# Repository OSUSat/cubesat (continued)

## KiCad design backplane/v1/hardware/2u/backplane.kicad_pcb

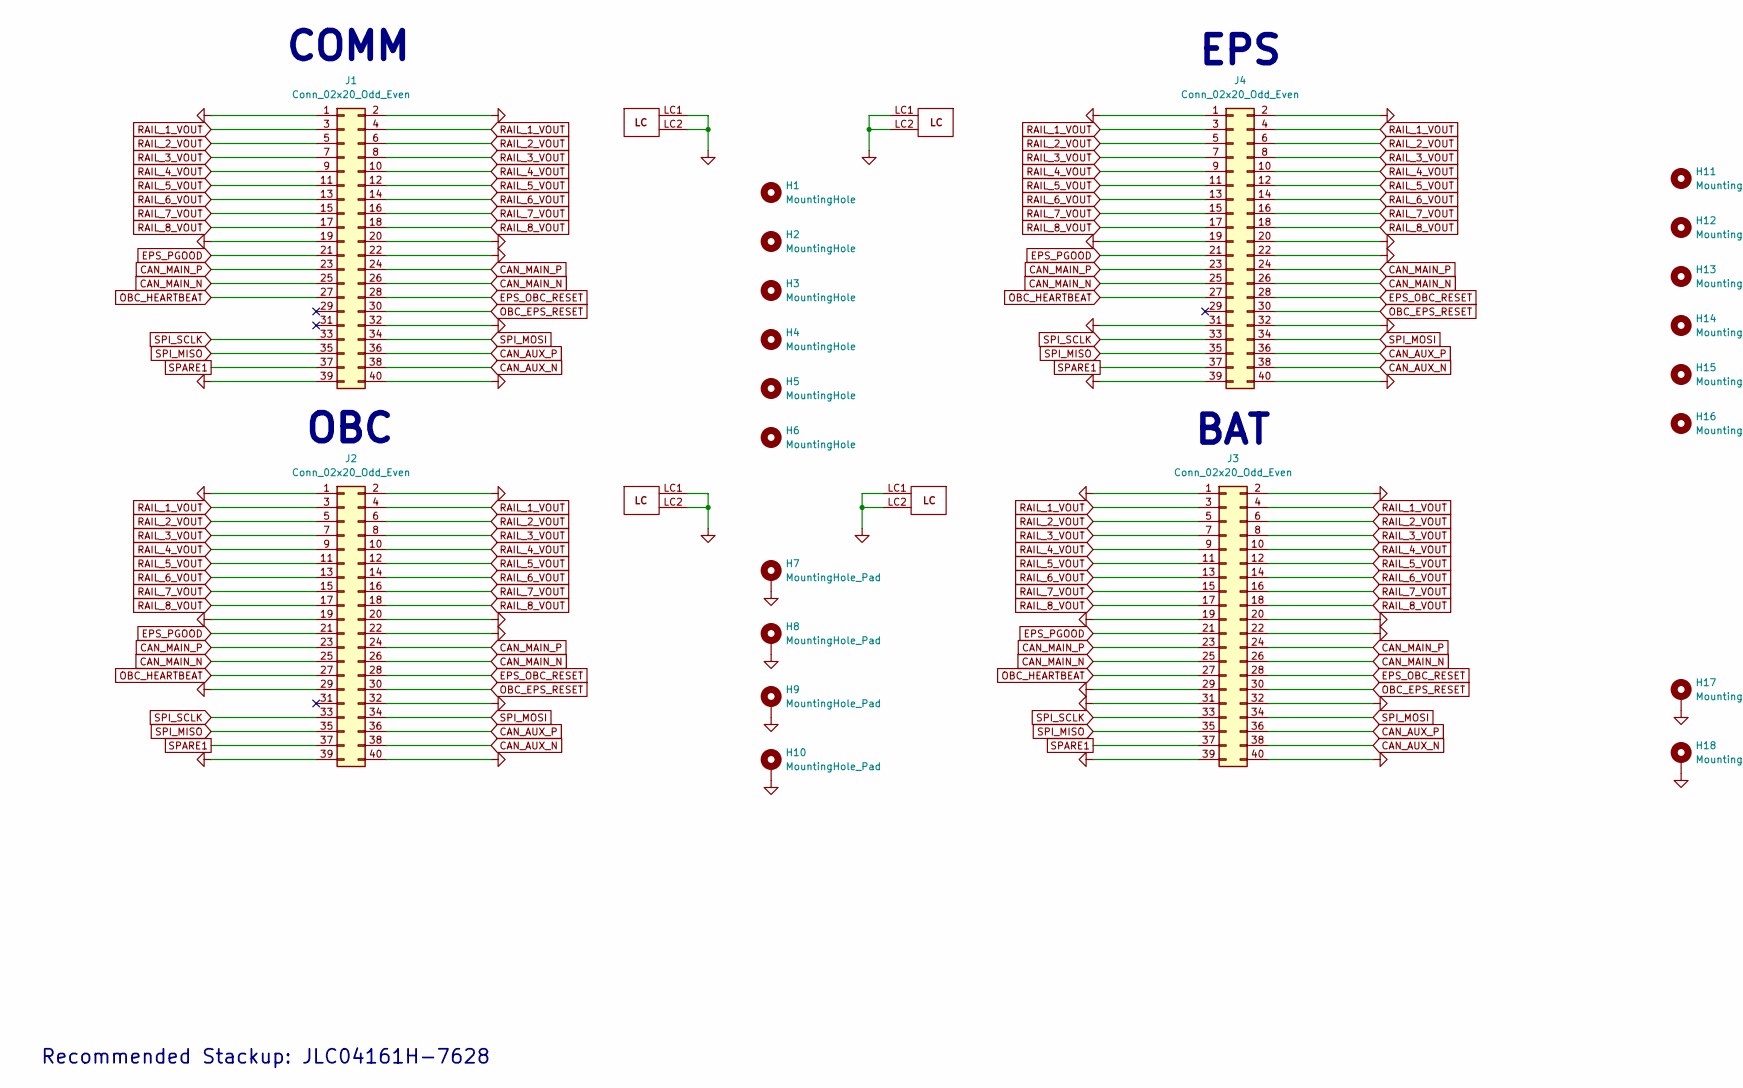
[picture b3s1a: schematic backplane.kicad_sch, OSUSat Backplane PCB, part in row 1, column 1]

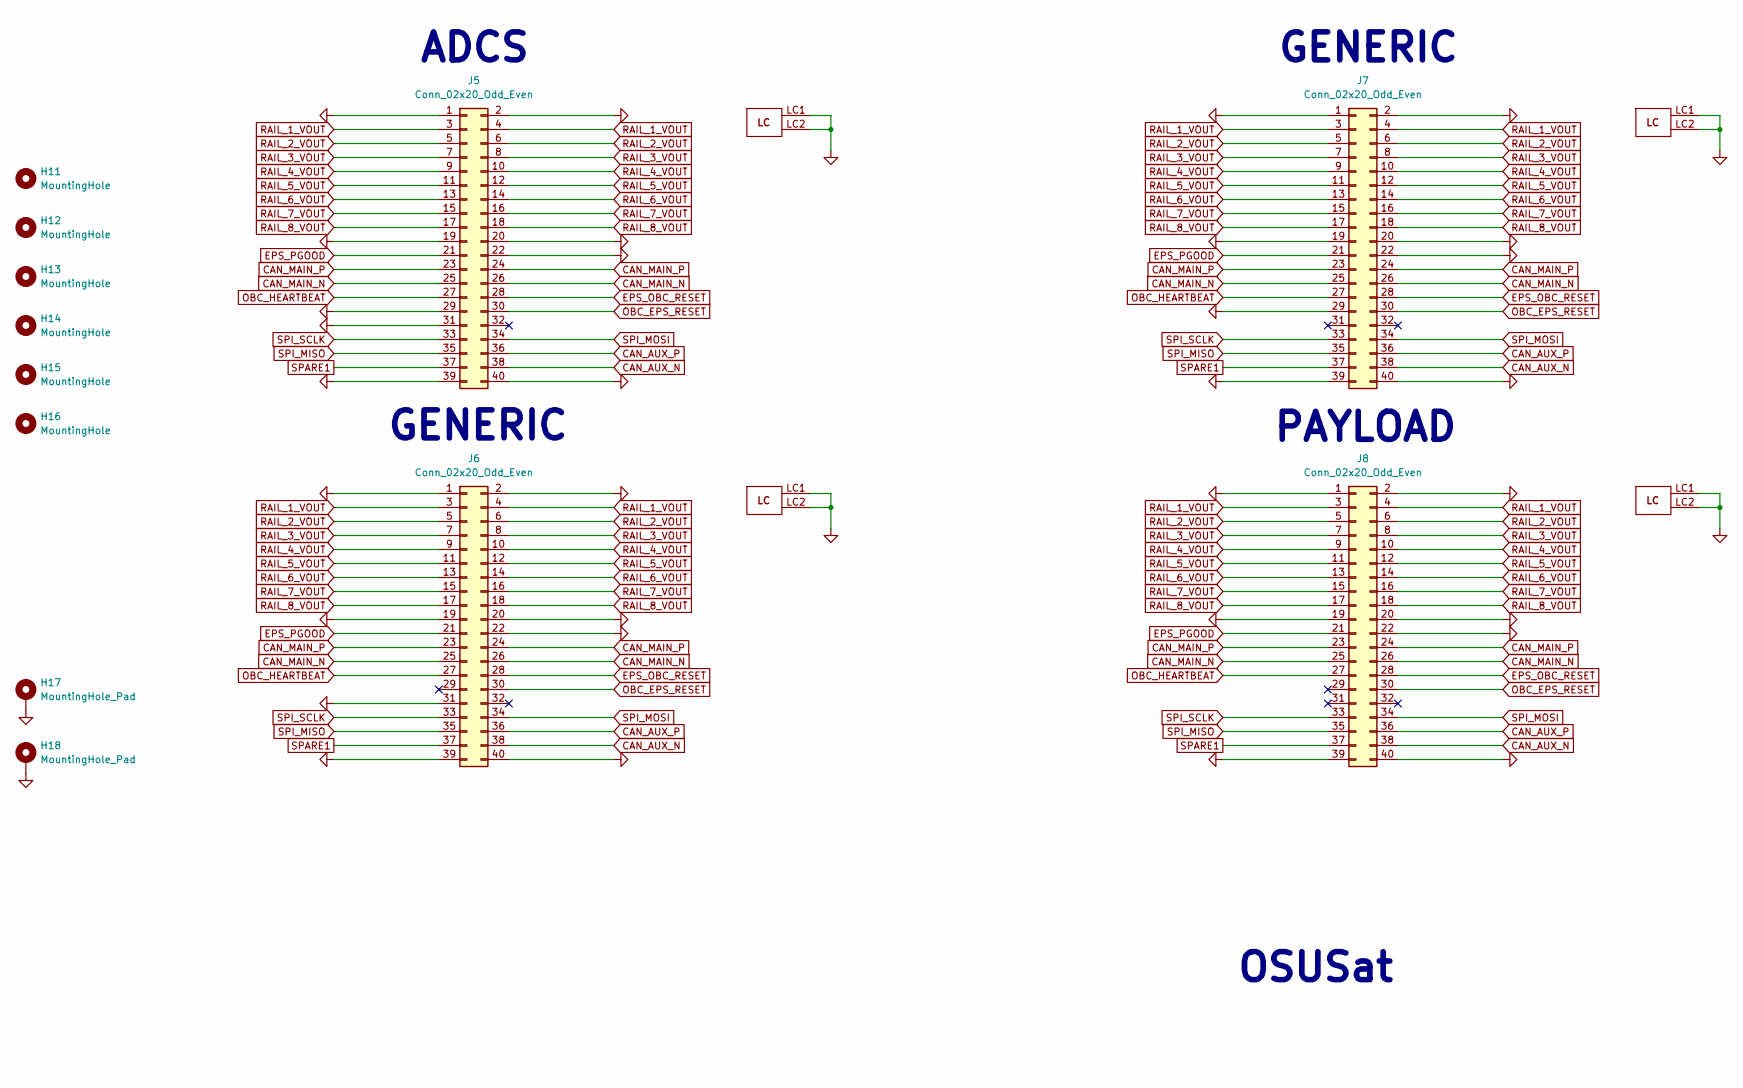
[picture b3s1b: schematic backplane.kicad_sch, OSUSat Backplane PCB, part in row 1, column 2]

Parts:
H1, H2, H3, H4, H5, H6, H11, H12, H13, H14, H15, H16: MountingHole; MountingHole_4.3mm_M4
H7, H8, H9, H10, H17, H18: MountingHole_Pad; MountingHole_3.2mm_M3_Pad
J1, J2, J3, J4, J5, J6, J7, J8: Conn_02x20_Odd_Even; SFM-120-X1-XXX-D

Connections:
CAN_AUX_N: J1.38, J2.38, J3.38, J4.38, J5.38, J6.38, J7.38, J8.38
CAN_AUX_P: J1.36, J2.36, J3.36, J4.36, J5.36, J6.36, J7.36, J8.36
CAN_MAIN_N: J1.25, J1.26, J2.25, J2.26, J3.25, J3.26, J4.25, J4.26, J5.25, J5.26, J6.25, J6.26, J7.25, J7.26, J8.25, J8.26
CAN_MAIN_P: J1.23, J1.24, J2.23, J2.24, J3.23, J3.24, J4.23, J4.24, J5.23, J5.24, J6.23, J6.24, J7.23, J7.24, J8.23, J8.24
EPS_OBC_RESET: J1.28, J2.28, J3.28, J4.28, J5.28, J6.28, J7.28, J8.28
EPS_PGOOD: J1.21, J2.21, J3.21, J4.21, J5.21, J6.21, J7.21, J8.21
GND: H7.1 (1_1), H8.1 (1_1), H9.1 (1_1), H10.1 (1_1), H17.1 (1_1), H18.1 (1_1), J1.1, J1.2, J1.19, J1.20, J1.22, J1.32, J1.39, J1.40, J1.LC1, J1.LC2, J2.1, J2.2, J2.19, J2.20, J2.22, J2.29, J2.32, J2.39, J2.40, J2.LC1, J2.LC2, J3.1, J3.2, J3.19, J3.20, J3.22, J3.29, J3.31, J3.32, J3.39, J3.40, J3.LC1, J3.LC2, J4.1, J4.2, J4.19, J4.20, J4.22, J4.31, J4.32, J4.39, J4.40, J4.LC1, J4.LC2, J5.1, J5.2, J5.19, J5.20, J5.22, J5.29, J5.31, J5.39, J5.40, J5.LC1, J5.LC2, J6.1, J6.2, J6.19, J6.20, J6.22, J6.31, J6.39, J6.40, J6.LC1, J6.LC2, J7.1, J7.2, J7.19, J7.20, J7.22, J7.29, J7.39, J7.40, J7.LC1, J7.LC2, J8.1, J8.2, J8.19, J8.20, J8.22, J8.39, J8.40, J8.LC1, J8.LC2
OBC_EPS_RESET: J1.30, J2.30, J3.30, J4.30, J5.30, J6.30, J7.30, J8.30
OBC_HEARTBEAT: J1.27, J2.27, J3.27, J4.27, J5.27, J6.27, J7.27, J8.27
RAIL_1_VOUT: J1.3, J1.4, J2.3, J2.4, J3.3, J3.4, J4.3, J4.4, J5.3, J5.4, J6.3, J6.4, J7.3, J7.4, J8.3, J8.4
RAIL_2_VOUT: J1.5, J1.6, J2.5, J2.6, J3.5, J3.6, J4.5, J4.6, J5.5, J5.6, J6.5, J6.6, J7.5, J7.6, J8.5, J8.6
RAIL_3_VOUT: J1.7, J1.8, J2.7, J2.8, J3.7, J3.8, J4.7, J4.8, J5.7, J5.8, J6.7, J6.8, J7.7, J7.8, J8.7, J8.8
RAIL_4_VOUT: J1.9, J1.10, J2.9, J2.10, J3.9, J3.10, J4.9, J4.10, J5.9, J5.10, J6.9, J6.10, J7.9, J7.10, J8.9, J8.10
RAIL_5_VOUT: J1.11, J1.12, J2.11, J2.12, J3.11, J3.12, J4.11, J4.12, J5.11, J5.12, J6.11, J6.12, J7.11, J7.12, J8.11, J8.12
RAIL_6_VOUT: J1.13, J1.14, J2.13, J2.14, J3.13, J3.14, J4.13, J4.14, J5.13, J5.14, J6.13, J6.14, J7.13, J7.14, J8.13, J8.14
RAIL_7_VOUT: J1.15, J1.16, J2.15, J2.16, J3.15, J3.16, J4.15, J4.16, J5.15, J5.16, J6.15, J6.16, J7.15, J7.16, J8.15, J8.16
RAIL_8_VOUT: J1.17, J1.18, J2.17, J2.18, J3.17, J3.18, J4.17, J4.18, J5.17, J5.18, J6.17, J6.18, J7.17, J7.18, J8.17, J8.18
SPARE1: J1.37, J2.37, J3.37, J4.37, J5.37, J6.37, J7.37, J8.37
SPI_MISO: J1.35, J2.35, J3.35, J4.35, J5.35, J6.35, J7.35, J8.35
SPI_MOSI: J1.34, J2.34, J3.34, J4.34, J5.34, J6.34, J7.34, J8.34
SPI_SCLK: J1.33, J2.33, J3.33, J4.33, J5.33, J6.33, J7.33, J8.33

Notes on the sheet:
Recommended Stackup: JLC04161H-7628
GENERIC
OSUSat
EPS
COMM
PAYLOAD
OBC
BAT
ADCS

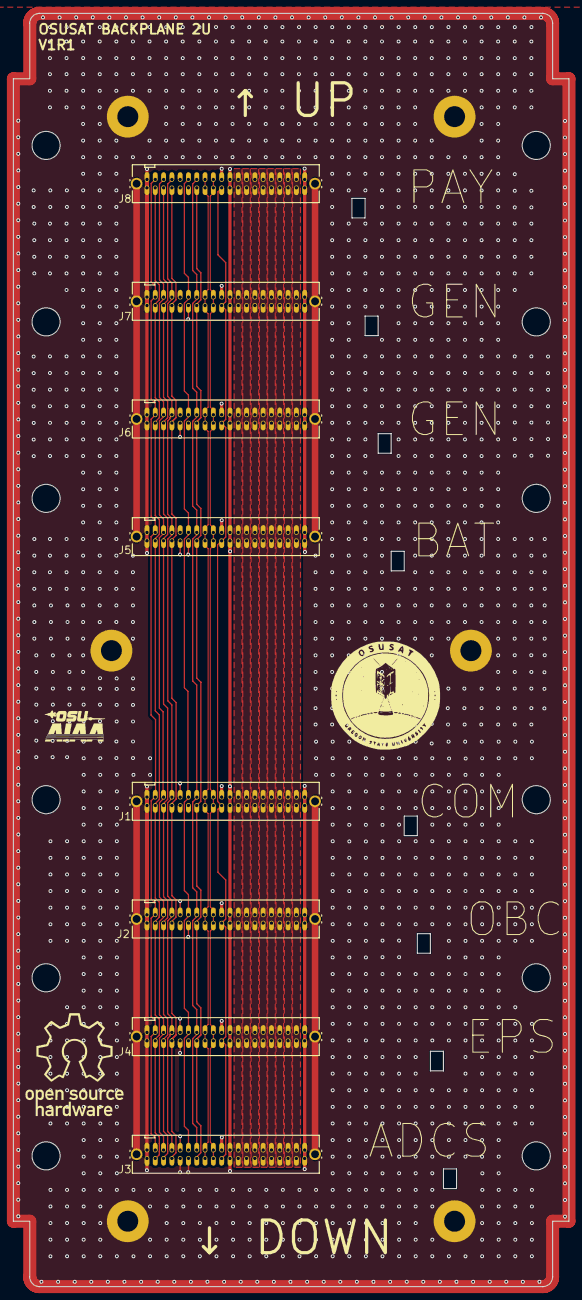
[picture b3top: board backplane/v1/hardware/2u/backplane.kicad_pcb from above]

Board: 4 copper layers, 85.0 x 194.8 mm, 26 parts (0 on the bottom side), 21 nets.

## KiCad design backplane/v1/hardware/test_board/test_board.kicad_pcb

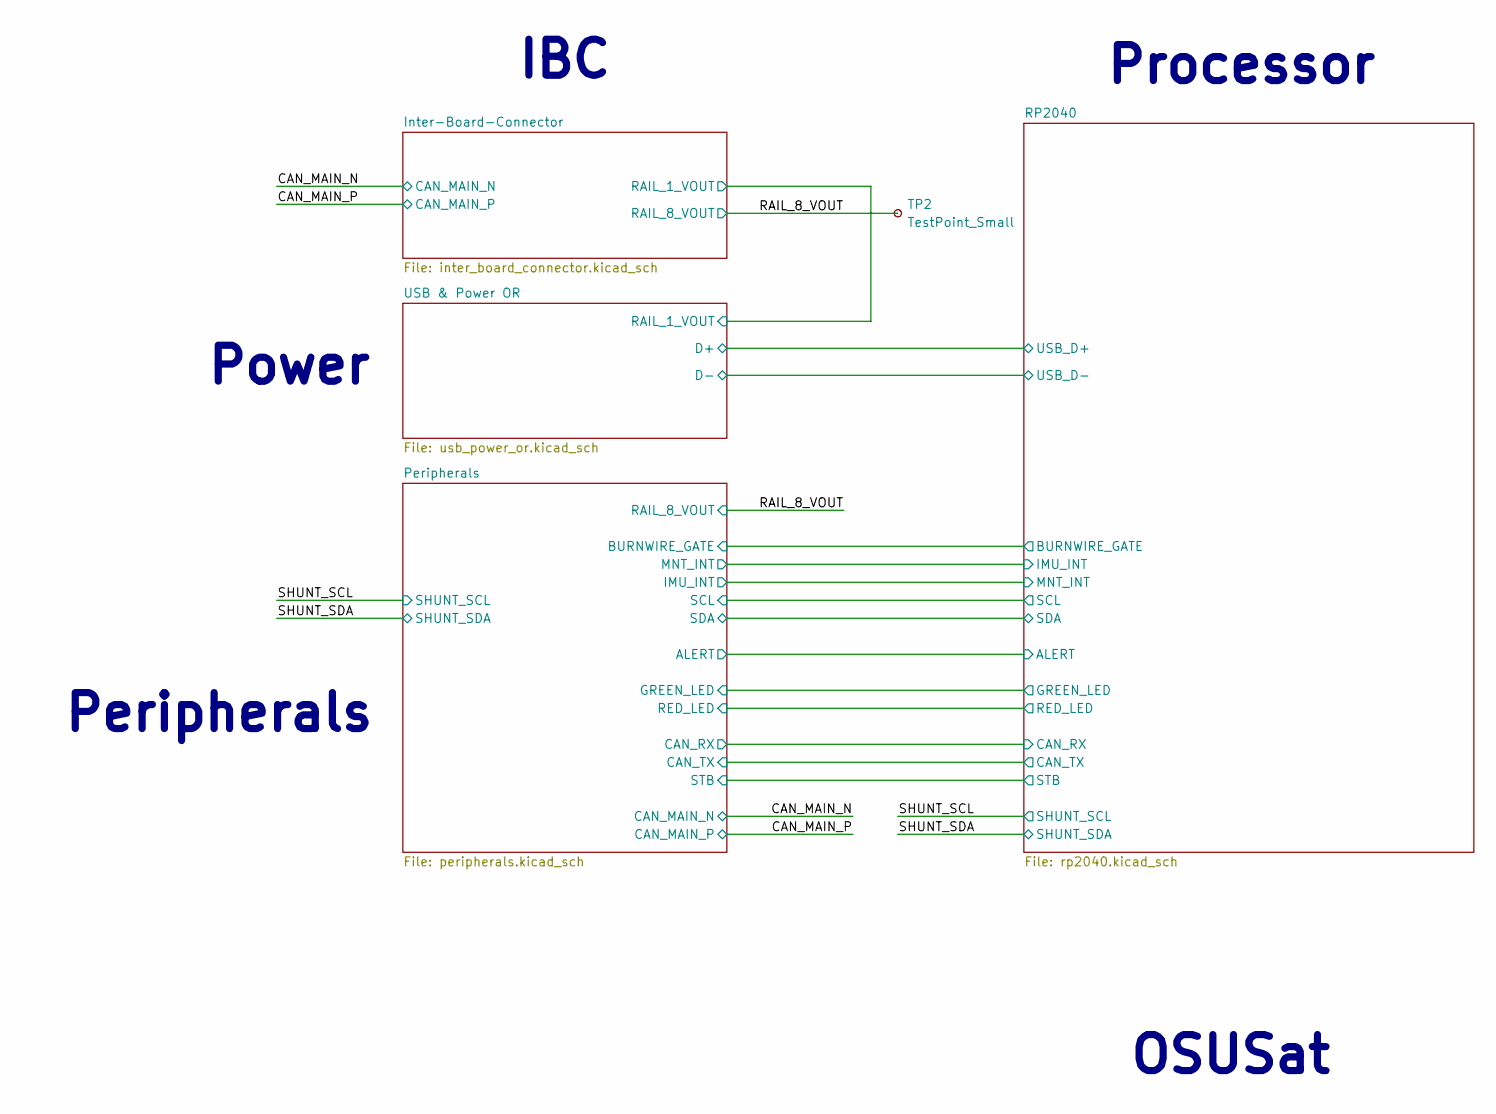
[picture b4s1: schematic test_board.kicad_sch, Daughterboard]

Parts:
TP2: TestPoint_Small; TestPoint_Pad_D1.0mm

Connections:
/RAIL_8_VOUT: TP2.1 (1_1); also elsewhere on the board

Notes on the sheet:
Processor
OSUSat
Peripherals
IBC
Power

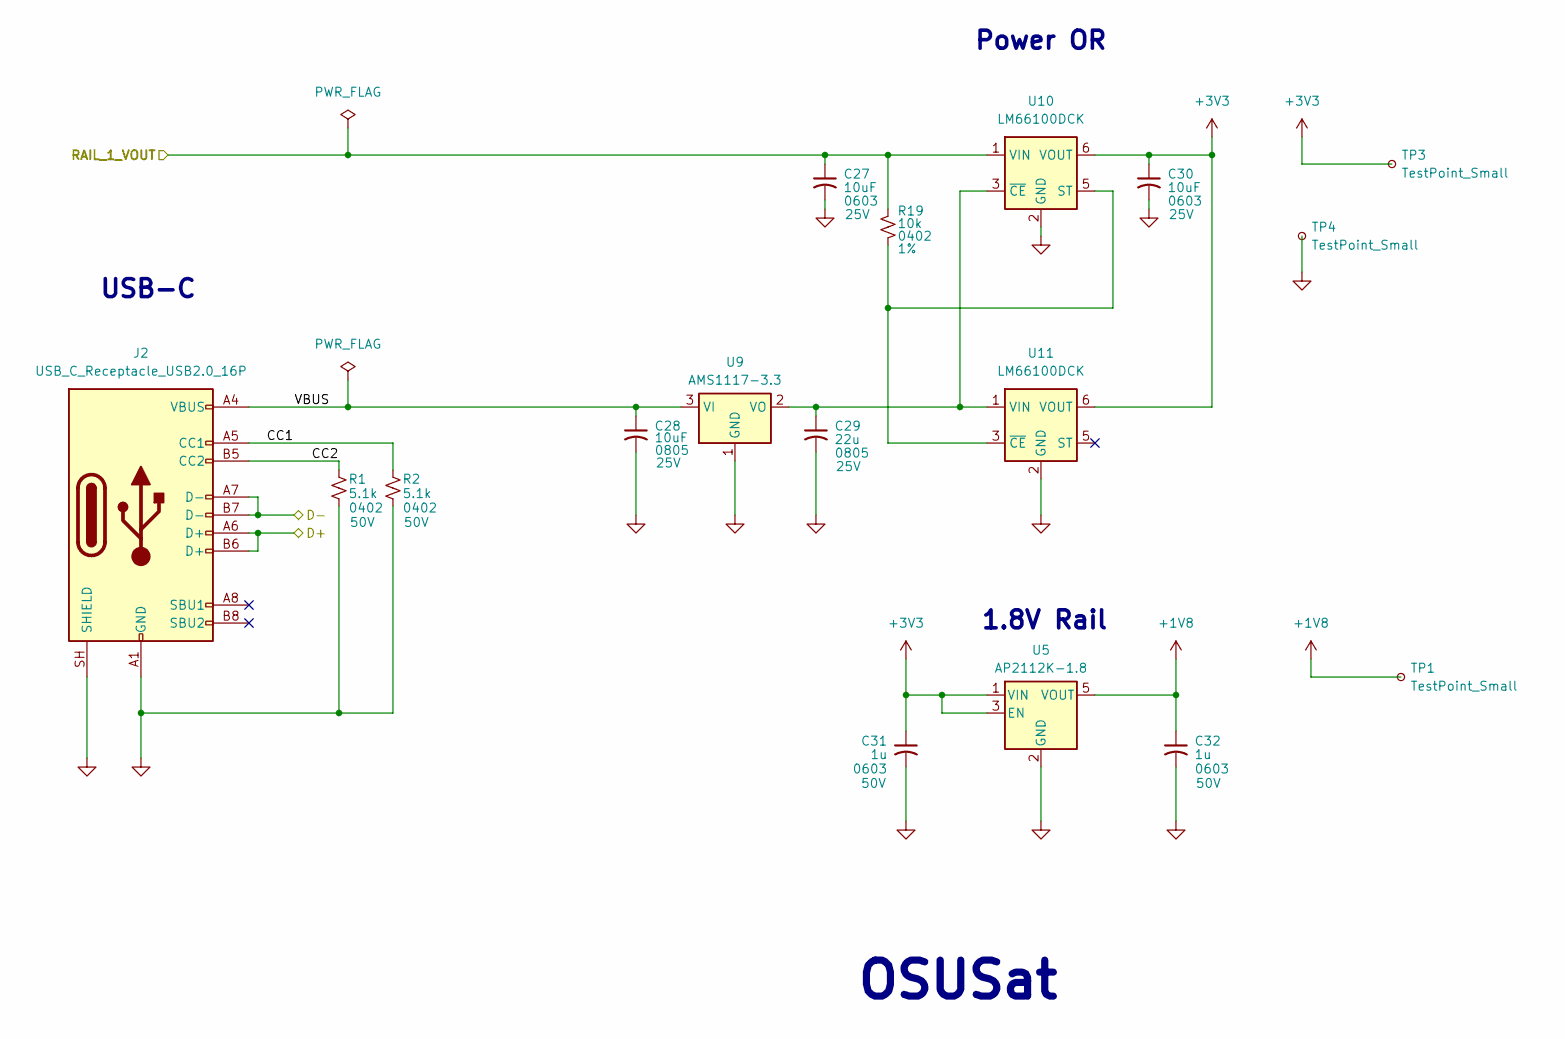
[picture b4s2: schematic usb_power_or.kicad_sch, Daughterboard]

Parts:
C27, C30: 10uF; C_0603_1608Metric; Breakdown Voltage 25V; LCSC PN C96446
C28: 10uF; C_0805_2012Metric; Breakdown Voltage 25V; LCSC PN C15850
C29: 22u; C_0805_2012Metric; Breakdown Voltage 25V; LCSC PN C45783
C31, C32: 1u; C_0603_1608Metric; Breakdown Voltage 50V; LCSC PN C15849
J2: USB_C_Receptacle_USB2.0_16P; USB_C_Receptacle_HRO_TYPE-C-31-M-12; LCSC PN C165948
R1, R2: 5.1k; R_0402_1005Metric; Breakdown Voltage 50V; LCSC PN C25905
R19: 10k; R_0402_1005Metric; Tolerance 1%; LCSC PN C25744
TP1, TP3, TP4: TestPoint_Small; TestPoint_Pad_D1.0mm
U5: AP2112K-1.8; SOT-23-5; LCSC PN C176944
U9: AMS1117-3.3; SOT-223-3_TabPin2; LCSC C6186
U10, U11: LM66100DCK; SOT-363_SC-70-6; LCSC C5219211

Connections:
+1V8: C32.1, TP1.1 (1_1), U5.5 (VOUT); also elsewhere on the board
+3V3: C30.1, C31.1, TP3.1 (1_1), U5.1 (VIN), U5.3 (EN), U10.6 (VOUT), U11.6 (VOUT); also elsewhere on the board
/Inter-Board-Connector/RAIL_1_VOUT: C27.1, R19.1, U10.1 (VIN); also elsewhere on the board
/RP2040/USB_D+: J2.A6 (D+), J2.B6 (D+); also elsewhere on the board
/RP2040/USB_D-: J2.A7 (D-), J2.B7 (D-); also elsewhere on the board
/USB & Power OR/CC1: J2.A5 (CC1), R2.1
/USB & Power OR/CC2: J2.B5 (CC2), R1.1
/USB & Power OR/VBUS: C28.1, J2.A4 (VBUS), J2.A9 (VBUS), J2.B4 (VBUS), J2.B9 (VBUS), U9.3 (VI)
GND: C27.2, C28.2, C29.2, C30.2, C31.2, C32.2, J2.A1 (GND), J2.A12 (GND), J2.B1 (GND), J2.B12 (GND), J2.SH (SHIELD), R1.2, R2.2, TP4.1 (1_1), U5.2 (GND), U9.1 (GND), U10.2 (GND), U11.2 (GND); also elsewhere on the board
unnamed: R19.2, U10.5 (ST), U11.3 (~CE)
unnamed: C29.1, U9.2 (VO), U10.3 (~CE), U11.1 (VIN)

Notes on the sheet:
Power OR
OSUSat
USB-C
1.8V Rail

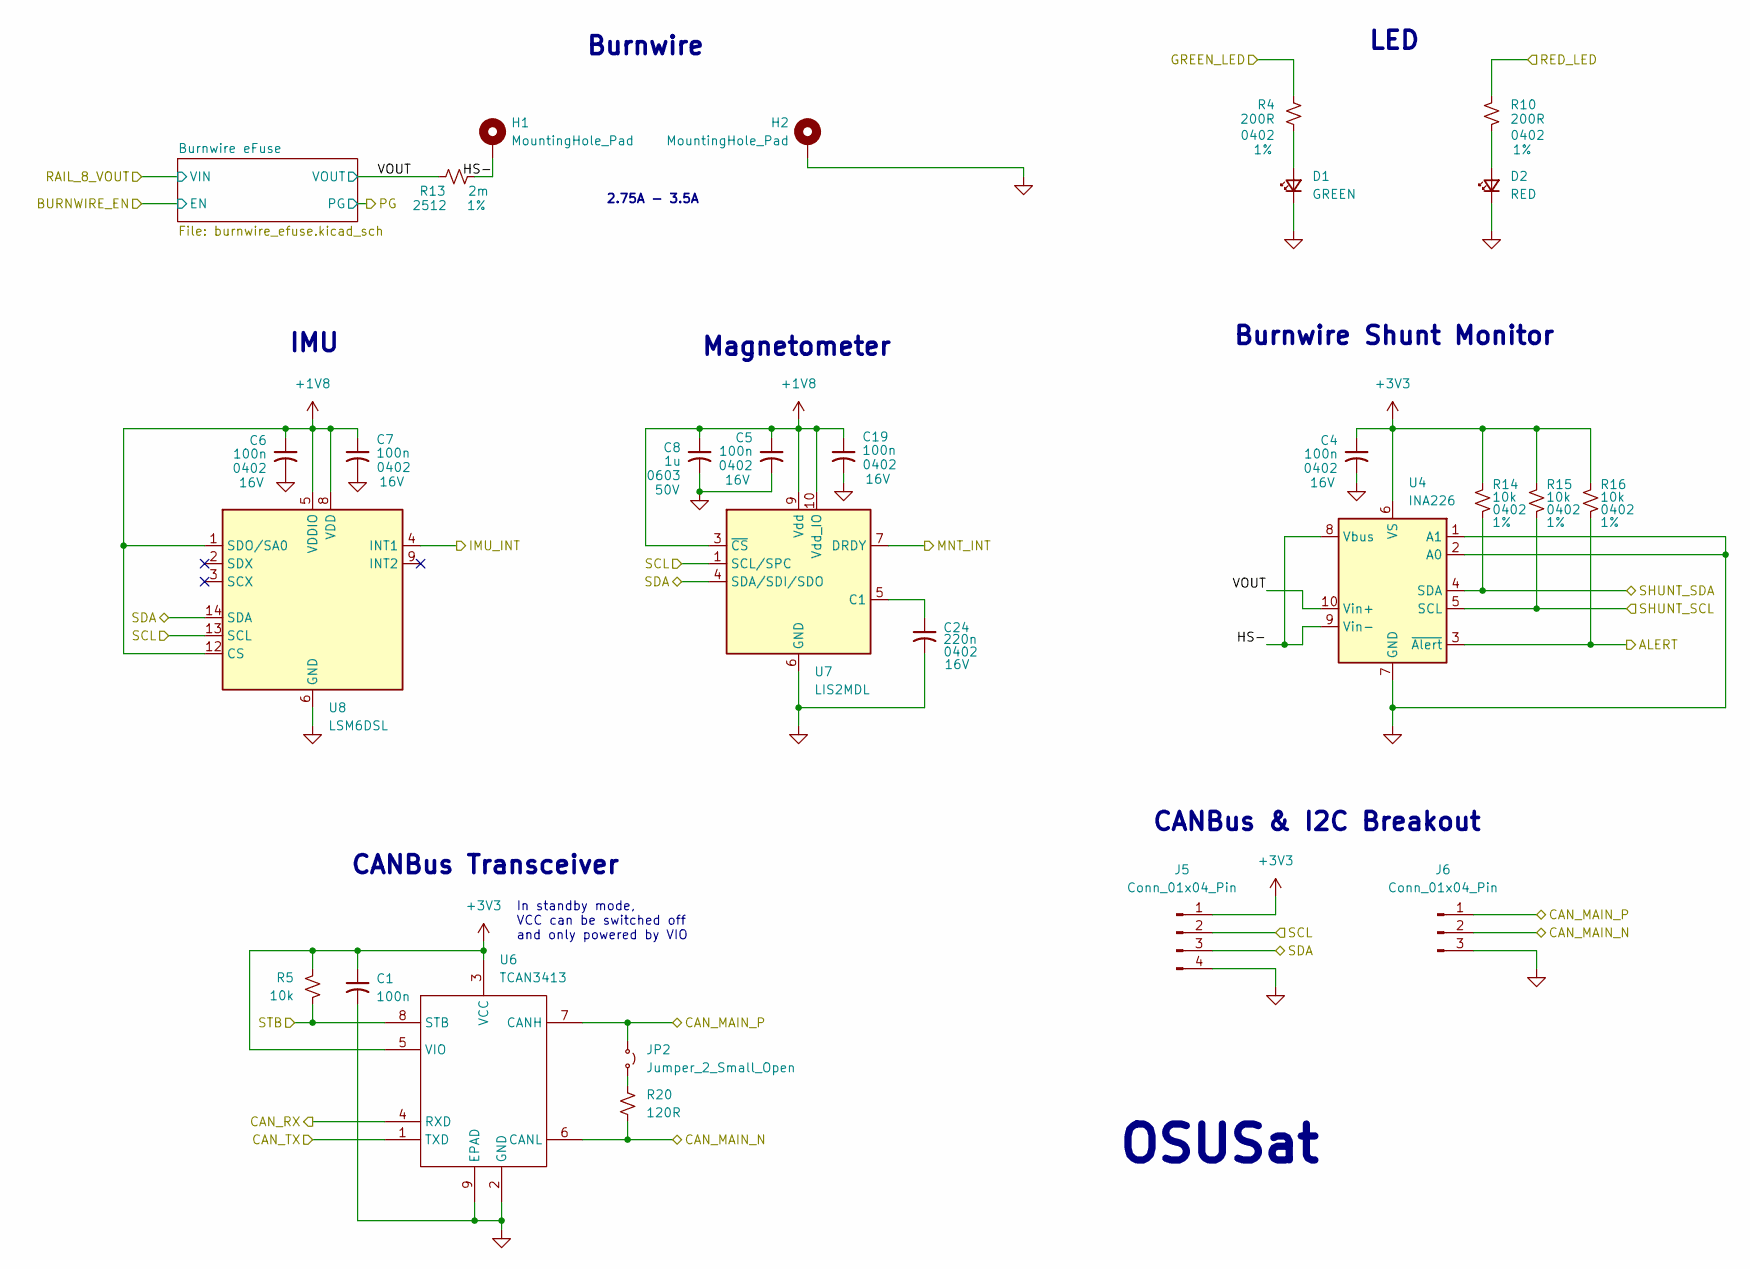
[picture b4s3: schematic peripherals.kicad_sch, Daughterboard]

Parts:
C1, C4, C5, C6, C7, C19: 100n; C_0402_1005Metric; Breakdown Voltage 16V; LCSC PN C1525
C8: 1u; C_0603_1608Metric; Breakdown Voltage 50V; LCSC PN C15849
C24: 220n; C_0402_1005Metric; Breakdown Voltage 16V; LCSC PN C16772
D1: GREEN; LED_0402_1005Metric
D2: RED; LED_0402_1005Metric
H1, H2: MountingHole_Pad; MountingHole_3.2mm_M3_Pad
J5: Conn_01x04_Pin; PinHeader_1x04_P2.54mm_Vertical
J6: Conn_01x04_Pin; PinHeader_1x03_P2.54mm_Vertical
JP2: Jumper_2_Small_Open; TestPoint_2Pads_Pitch2.54mm_Drill0.8mm
R4, R10: 200R; R_0402_1005Metric; Tolerance 1%; LCSC PN C25087
R5: 10k; R_0402_1005Metric; LCSC PN C25744
R13: 2m; R_2512_6332Metric; Tolerance 1%; LCSC PN C55591708
R14, R15, R16: 10k; R_0402_1005Metric; Tolerance 1%; LCSC PN C25744
R20: 120R; R_0402_1005Metric; LCSC PN C25079
U4: INA226; TSSOP-10_3x3mm_P0.5mm; LCSC PN C49851
U6: TCAN3413; VSON-8-1EP_3x3mm_P0.65mm_EP1.65x2.4mm; LCSC PN C22445415
U7: LIS2MDL; LGA-12_2x2mm_P0.5mm
U8: LSM6DSL; LGA-14_3x2.5mm_P0.5mm_LayoutBorder3x4y; LCSC PN C126672

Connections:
+1V8: C5.1, C6.1, C7.1, C8.1, C19.1, U7.3 (~CS), U7.9 (Vdd), U7.10 (Vdd_IO), U8.1 (SDO/SA0), U8.5 (VDDIO), U8.8 (VDD), U8.12 (CS); also elsewhere on the board
+3V3: C1.1, C4.1, J5.1, R5.1, R14.1, R15.1, R16.1, U4.6 (VS), U6.3 (VCC), U6.5 (VIO); also elsewhere on the board
/CAN_MAIN_N: J6.2, R20.2, U6.6 (CANL); also elsewhere on the board
/CAN_MAIN_P: J6.1, JP2.1 (A), U6.7 (CANH); also elsewhere on the board
/Peripherals/ALERT: R16.2, U4.3 (~Alert); also elsewhere on the board
/Peripherals/CAN_RX: U6.4 (RXD); also elsewhere on the board
/Peripherals/CAN_TX: U6.1 (TXD); also elsewhere on the board
/Peripherals/GREEN_LED: R4.1; also elsewhere on the board
/Peripherals/HS-: H1.1 (1_1), R13.2, U4.8 (Vbus), U4.9 (Vin-)
/Peripherals/IMU_INT: U8.4 (INT1); also elsewhere on the board
/Peripherals/MNT_INT: U7.7 (DRDY); also elsewhere on the board
/Peripherals/RED_LED: R10.1; also elsewhere on the board
/Peripherals/SCL: J5.2, U7.1 (SCL/SPC), U8.13 (SCL); also elsewhere on the board
/Peripherals/SDA: J5.3, U7.4 (SDA/SDI/SDO), U8.14 (SDA); also elsewhere on the board
/Peripherals/STB: R5.2, U6.8 (STB); also elsewhere on the board
/Peripherals/VOUT: R13.1, U4.10 (Vin+); also elsewhere on the board
/SHUNT_SCL: R15.2, U4.5 (SCL); also elsewhere on the board
/SHUNT_SDA: R14.2, U4.4 (SDA); also elsewhere on the board
GND: C1.2, C4.2, C5.2, C6.2, C7.2, C8.2, C19.2, C24.2, D1.1 (K), D2.1 (K), H2.1 (1_1), J5.4, J6.3, U4.1 (A1), U4.2 (A0), U4.7 (GND), U6.2 (GND), U6.9 (EPAD), U7.6 (GND), U7.8 (GND), U8.6 (GND), U8.7 (GND); also elsewhere on the board
unnamed: D1.2 (A), R4.2
unnamed: D2.2 (A), R10.2
unnamed: JP2.2 (B), R20.1
unnamed: C24.1, U7.5 (C1)

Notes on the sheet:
Magnetometer
CANBus & I2C Breakout
LED
Burnwire
In standby mode, VCC can be switched off and only powered by VIO
IMU
OSUSat
2.75A - 3.5A
Burnwire Shunt Monitor
CANBus Transceiver

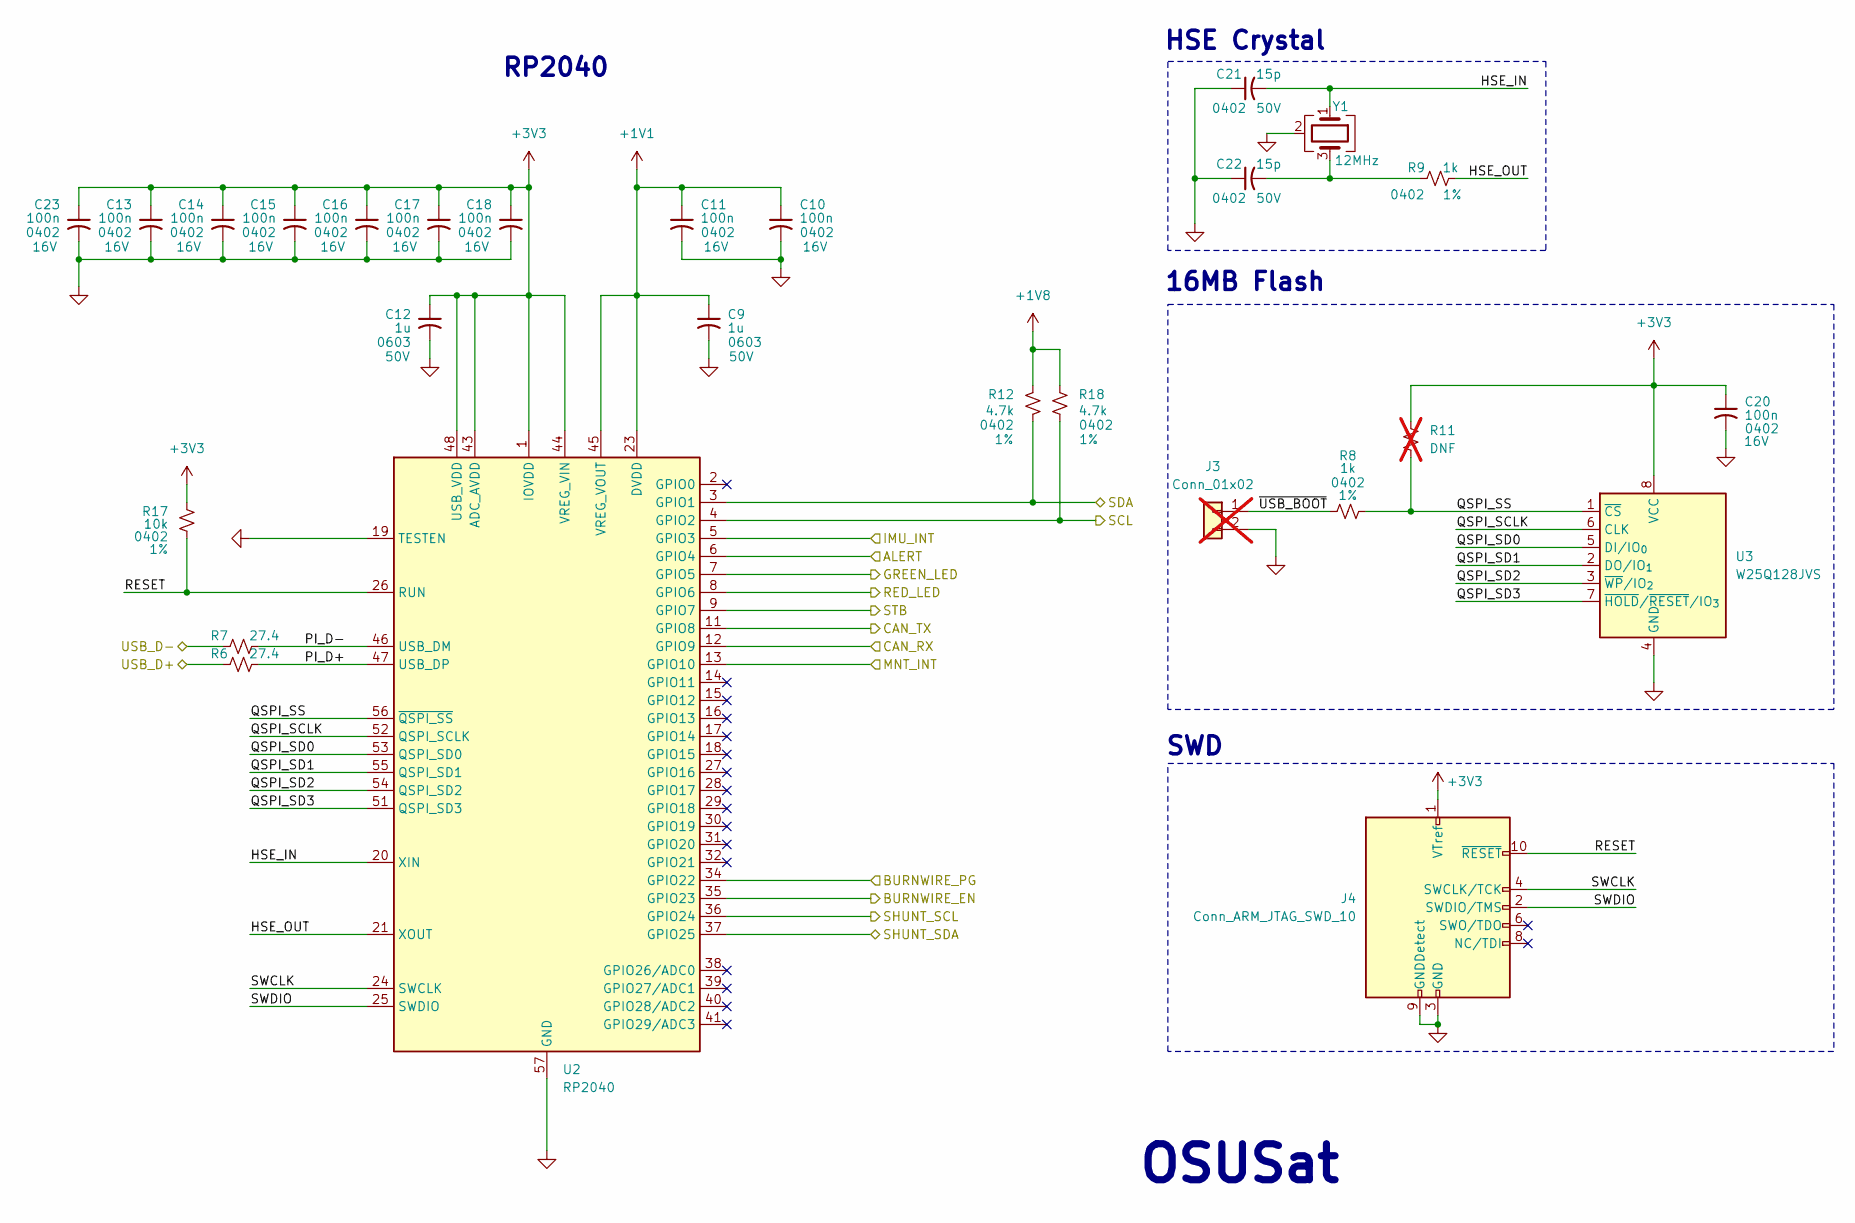
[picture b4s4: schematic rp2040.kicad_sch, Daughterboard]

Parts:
C9, C12: 1u; C_0603_1608Metric; Breakdown Voltage 50V; LCSC PN C15849
C10, C11, C13, C14, C15, C16, C17, C18, C20, C23: 100n; C_0402_1005Metric; Breakdown Voltage 16V; LCSC PN C1525
C21, C22: 15p; C_0402_1005Metric; Breakdown Voltage 50V; LCSC PN C1548
J3: Conn_01x02; PinHeader_1x02_P2.54mm_Vertical; not fitted
J4: Conn_ARM_JTAG_SWD_10; PinHeader_2x05_P1.27mm_Vertical_SMD; LCSC PN C54950779
R6, R7: 27.4; R_0402_1005Metric; LCSC PN C177713
R8, R9: 1k; R_0402_1005Metric; Tolerance 1%; LCSC PN C21190
R11: DNF; R_0402_1005Metric; not fitted
R12, R18: 4.7k; R_0402_1005Metric; Tolerance 1%; LCSC PN C25900
R17: 10k; R_0402_1005Metric; Tolerance 1%; LCSC PN C25744
U2: RP2040; QFN-56-1EP_7x7mm_P0.4mm_EP3.2x3.2mm; LCSC PN C2040
U3: W25Q128JVS; SOIC-8_5.3x5.3mm_P1.27mm; LCSC PN C97521
Y1: 12MHz; Crystal_SMD_3225-4Pin_3.2x2.5mm; LCSC PN C9002

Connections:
+1V1: C9.1, C10.1, C11.1, U2.23 (DVDD), U2.45 (VREG_VOUT), U2.50 (DVDD)
+1V8: R12.1, R18.1; also elsewhere on the board
+3V3: C12.1, C13.1, C14.1, C15.1, C16.1, C17.1, C18.1, C20.1, C23.1, J4.1 (VTref), R11.1, R17.1, U2.1 (IOVDD), U2.10 (IOVDD), U2.22 (IOVDD), U2.33 (IOVDD), U2.42 (IOVDD), U2.43 (ADC_AVDD), U2.44 (VREG_VIN), U2.48 (USB_VDD), U2.49 (IOVDD), U3.8 (VCC); also elsewhere on the board
/Peripherals/ALERT: U2.6 (GPIO4); also elsewhere on the board
/Peripherals/BURNWIRE_EN: U2.35 (GPIO23); also elsewhere on the board
/Peripherals/CAN_RX: U2.12 (GPIO9); also elsewhere on the board
/Peripherals/CAN_TX: U2.11 (GPIO8); also elsewhere on the board
/Peripherals/GREEN_LED: U2.7 (GPIO5); also elsewhere on the board
/Peripherals/IMU_INT: U2.13 (GPIO10); also elsewhere on the board
/Peripherals/MNT_INT: U2.5 (GPIO3); also elsewhere on the board
/Peripherals/PG: U2.34 (GPIO22); also elsewhere on the board
/Peripherals/RED_LED: U2.8 (GPIO6); also elsewhere on the board
/Peripherals/SCL: R18.2, U2.4 (GPIO2); also elsewhere on the board
/Peripherals/SDA: R12.2, U2.3 (GPIO1); also elsewhere on the board
/Peripherals/STB: U2.9 (GPIO7); also elsewhere on the board
/RP2040/HSE_IN: C21.2, U2.20 (XIN), Y1.1
/RP2040/HSE_OUT: R9.2, U2.21 (XOUT)
/RP2040/PI_D+: R6.2, U2.47 (USB_DP)
/RP2040/PI_D-: R7.2, U2.46 (USB_DM)
/RP2040/QSPI_SCLK: U2.52 (QSPI_SCLK), U3.6 (CLK)
/RP2040/QSPI_SD0: U2.53 (QSPI_SD0), U3.5 (DI/IO_{0})
/RP2040/QSPI_SD1: U2.55 (QSPI_SD1), U3.2 (DO/IO_{1})
/RP2040/QSPI_SD2: U2.54 (QSPI_SD2), U3.3 (~WP/IO_{2})
/RP2040/QSPI_SD3: U2.51 (QSPI_SD3), U3.7 (~HOLD/~RESET/IO_{3})
/RP2040/QSPI_SS: R8.2, R11.2, U2.56 (~QSPI_SS), U3.1 (~CS)
/RP2040/RESET: J4.10 (~RESET), R17.2, U2.26 (RUN)
/RP2040/SWCLK: J4.4 (SWCLK/TCK), U2.24 (SWCLK)
/RP2040/SWDIO: J4.2 (SWDIO/TMS), U2.25 (SWDIO)
/RP2040/USB_D+: R6.1; also elsewhere on the board
/RP2040/USB_D-: R7.1; also elsewhere on the board
/RP2040/~USB_BOOT: J3.1, R8.1
/SHUNT_SCL: U2.36 (GPIO24); also elsewhere on the board
/SHUNT_SDA: U2.37 (GPIO25); also elsewhere on the board
GND: C9.2, C10.2, C11.2, C12.2, C13.2, C14.2, C15.2, C16.2, C17.2, C18.2, C20.2, C21.1, C22.1, C23.2, J3.2, J4.3 (GND), J4.5 (GND), J4.9 (GNDDetect), U2.19 (TESTEN), U2.57 (GND), U3.4 (GND), Y1.2 (G), Y1.4 (G); also elsewhere on the board
unnamed: C22.2, R9.1, Y1.3

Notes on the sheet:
SWD
16MB Flash
HSE Crystal
OSUSat
RP2040

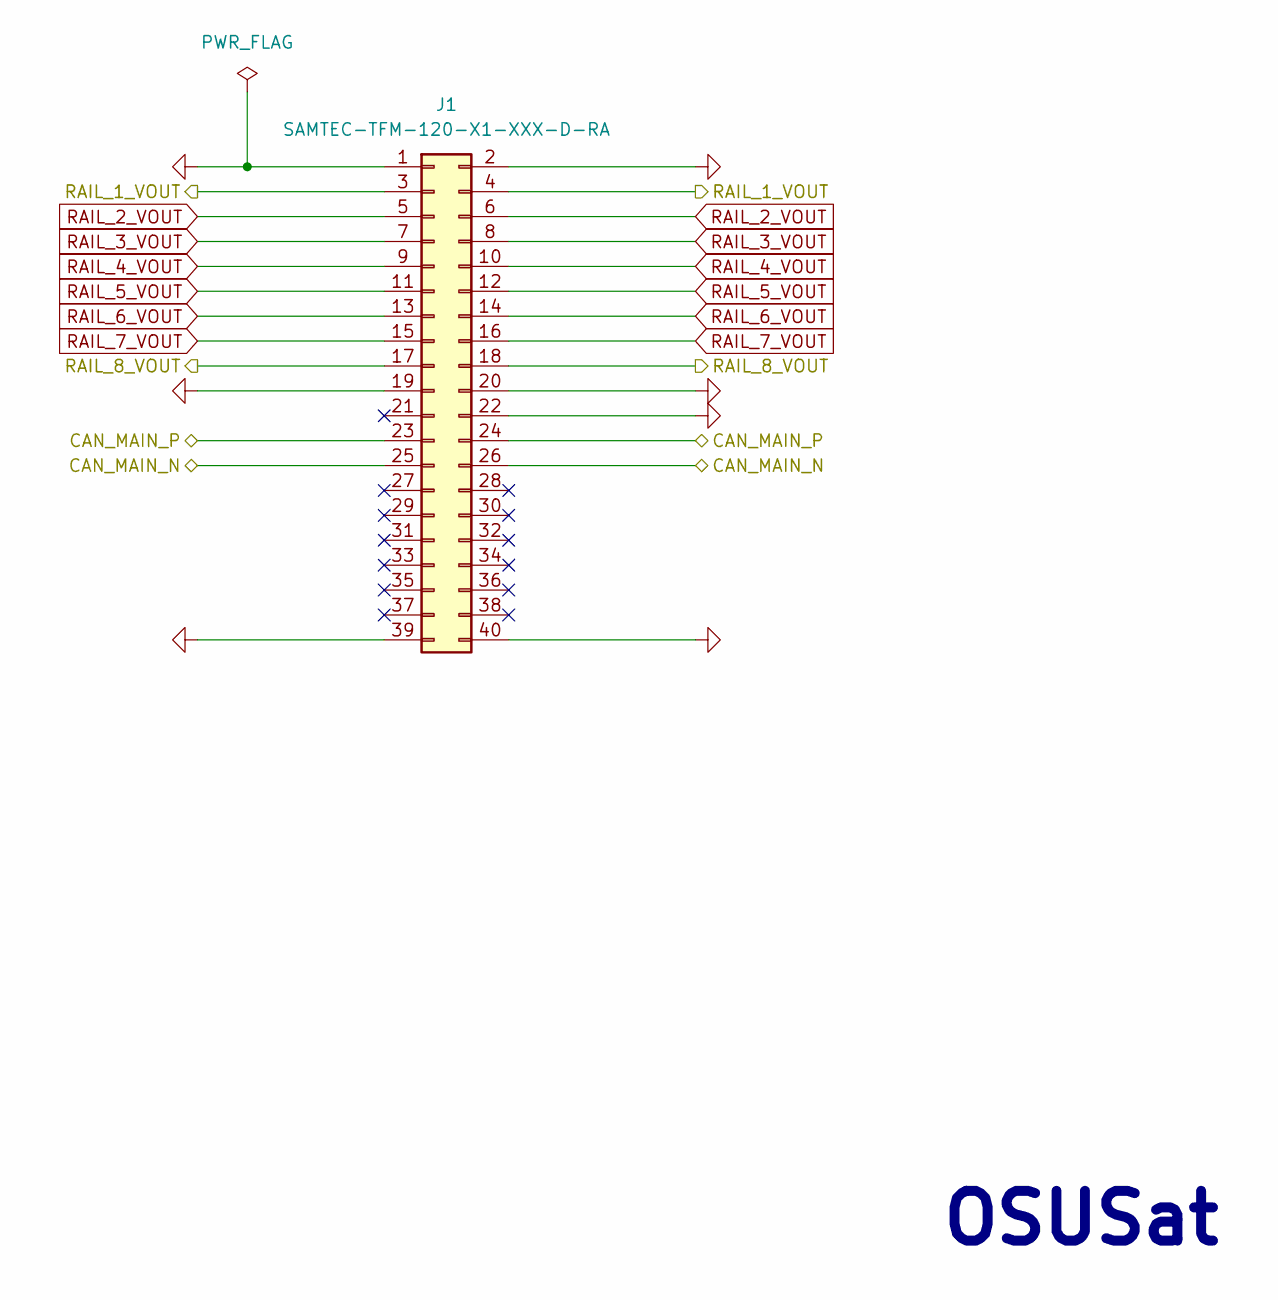
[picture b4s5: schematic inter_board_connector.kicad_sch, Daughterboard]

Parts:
J1: SAMTEC-TFM-120-X1-XXX-D-RA; J-SAMTEC-TFM-120-X1-XXX-D-RA

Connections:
/CAN_MAIN_N: J1.25, J1.26; also elsewhere on the board
/CAN_MAIN_P: J1.23, J1.24; also elsewhere on the board
/Inter-Board-Connector/RAIL_1_VOUT: J1.3, J1.4; also elsewhere on the board
/RAIL_8_VOUT: J1.17, J1.18; also elsewhere on the board
GND: J1.1, J1.2, J1.19, J1.20, J1.22, J1.39, J1.40; also elsewhere on the board
RAIL_2_VOUT: J1.5, J1.6
RAIL_3_VOUT: J1.7, J1.8
RAIL_4_VOUT: J1.9, J1.10
RAIL_5_VOUT: J1.11, J1.12
RAIL_6_VOUT: J1.13, J1.14
RAIL_7_VOUT: J1.15, J1.16

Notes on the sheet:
OSUSat
